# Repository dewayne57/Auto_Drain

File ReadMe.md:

# Air Compressor Automatic Drain
This project is an adaptive air compressor automatic drain system.  There are examples of products
on the market that use a timer to cycle a solenoid valve on the tank drain to release any moisture
that has condensed at the bottom of the tank.  The problem with these devices is that they cycle 
periodically (such as every 10 minutes) wether they need to or not.  For compressors that run only
sporadically, such as in a home shop, this causes aire loss and needless extra cycling of the compressor.

What this project does is sense when the compressor runs, then start a timer after it shuts off.
After some period of time (to allow condensant to accumulate), the drain valve is cycled.  The 
drain valve is then cycled again 1 hour after the last run to drain any additional accumulated 
condenstant.  After that, the drain valve is not cycled again until the compressor is run 
again.  This allows the system to efficiently drain the condensant water without needlessly 
cycling the drain valve.

## Algorithm 

### Assumptions/Conventions
- The compressor (or other sensed system) is identified as the "controlling" load. 
- The valve (or other driven system) is identified as the "controlled" load.
- The operation of the system is controlled by a state machine. 

### State Machine

| State (name)   | Stopped  | Running | Timeout |
| -------------- | -------- | ------- | ------- |
| S0 (Idle)      | S0       | S1      | S0      |
| S1 (Armed)     | S2       | S1      | S0      |
| S2 (Triggered) | S2       | S1      | S3      | 
| S3 (Drain)     | S0,S4(1) | S1      | S0      |
| S4 (Followup)  | S4       | S1      | S5      |
| S5 (Drain2)    | S0       | S1      | S0      |

- S0: Represents the idle state, where the system is waiting on the detection of the 
  controlling load to be turned on.  This is the initial state the system enters 
  after power on or a watchdog reset.
- S1: Represents the "armed" state where the controlling load has been detected to 
  be running.  As long as the controlling load is running, the system will be in this
  state. The armed state is entered from any state when the controlling load is 
  running. 
- S2: Represents the triggered state after the controlling load has stopped running
  and represents the start of the initial countdown period to operate the drain. If 
  the controlling load does not restart before the countdown timer expires, the 
  system will transition to the draining state. 
- S3: Represents the "draining" state.  This is where the drain valve is opened 
  for one second to drain the condensant water from the tank (or other operation 
  depending on application). Once the draining time has expired, the system will 
  transition to either idle or followup state (S0 or S4, see Note 1). 
- S4: This represents the followup countdown interval.  It is entered only after 
  a successfull drain cycle and  the followup  time intervals are selected by the 
  option switches.
- S5: Represents the followup drain cycle, which is initiated some time interval
  after a successful initial drain cycle if selected by the option switches. 

### Notes
1. Either S0 (Idle) or S4 (Followup) states are entered after an initial 
   drain cycle has occurred based on the setting of the option switches.  If the 
   option switches indicate no followup drain cycle, then the machine transitions
   to the idle (S0) state.  If the option switches indicate a followup drain 
   interval, the transition is to the S4 state and the followup countdown 
   interval timer is started.
2. If the controlling load is restarted at any time, any current countdown 
   interval is stopped and the state machine immediately enters the Armed 
   (s1) state.

### Option Switches: 
The option switches are a 4-position DIP switch divided into two 2-bit groups.
The first group (bits 0..1) represent the triggered countdown interval, and are
specified as: 
- 00: Cycle immediately after turn off.  There is no triggered delay, and 
  the state machine immediately cycles to the Drain (S3) state. 
- 01: The system will remain in the triggered state for 10 minutes, then 
  transition to the Drain (s3) state.
- 10: The system will remain in the triggered state for 30 minutes, then 
  transition to the Drain (S3) state. 
- 11: The system will remain in the triggered state for 1 hour (60 minutes), 
  then transition to the Drain (S3) state;

The second pair of bits (2..3) indicate the followup drain cycle, if any. 
- 00: No follow up cycle is to be used.  Transition to the Idle (S0) state
- 01: An additional followup drain cycle will occur 1 hour after the drain cycle.
- 10: An additional followup drain cycle will occur 2 hours after the drain cycle.
- 11: An additional followup drain cycle will occur 3 hours after the drain cycle.

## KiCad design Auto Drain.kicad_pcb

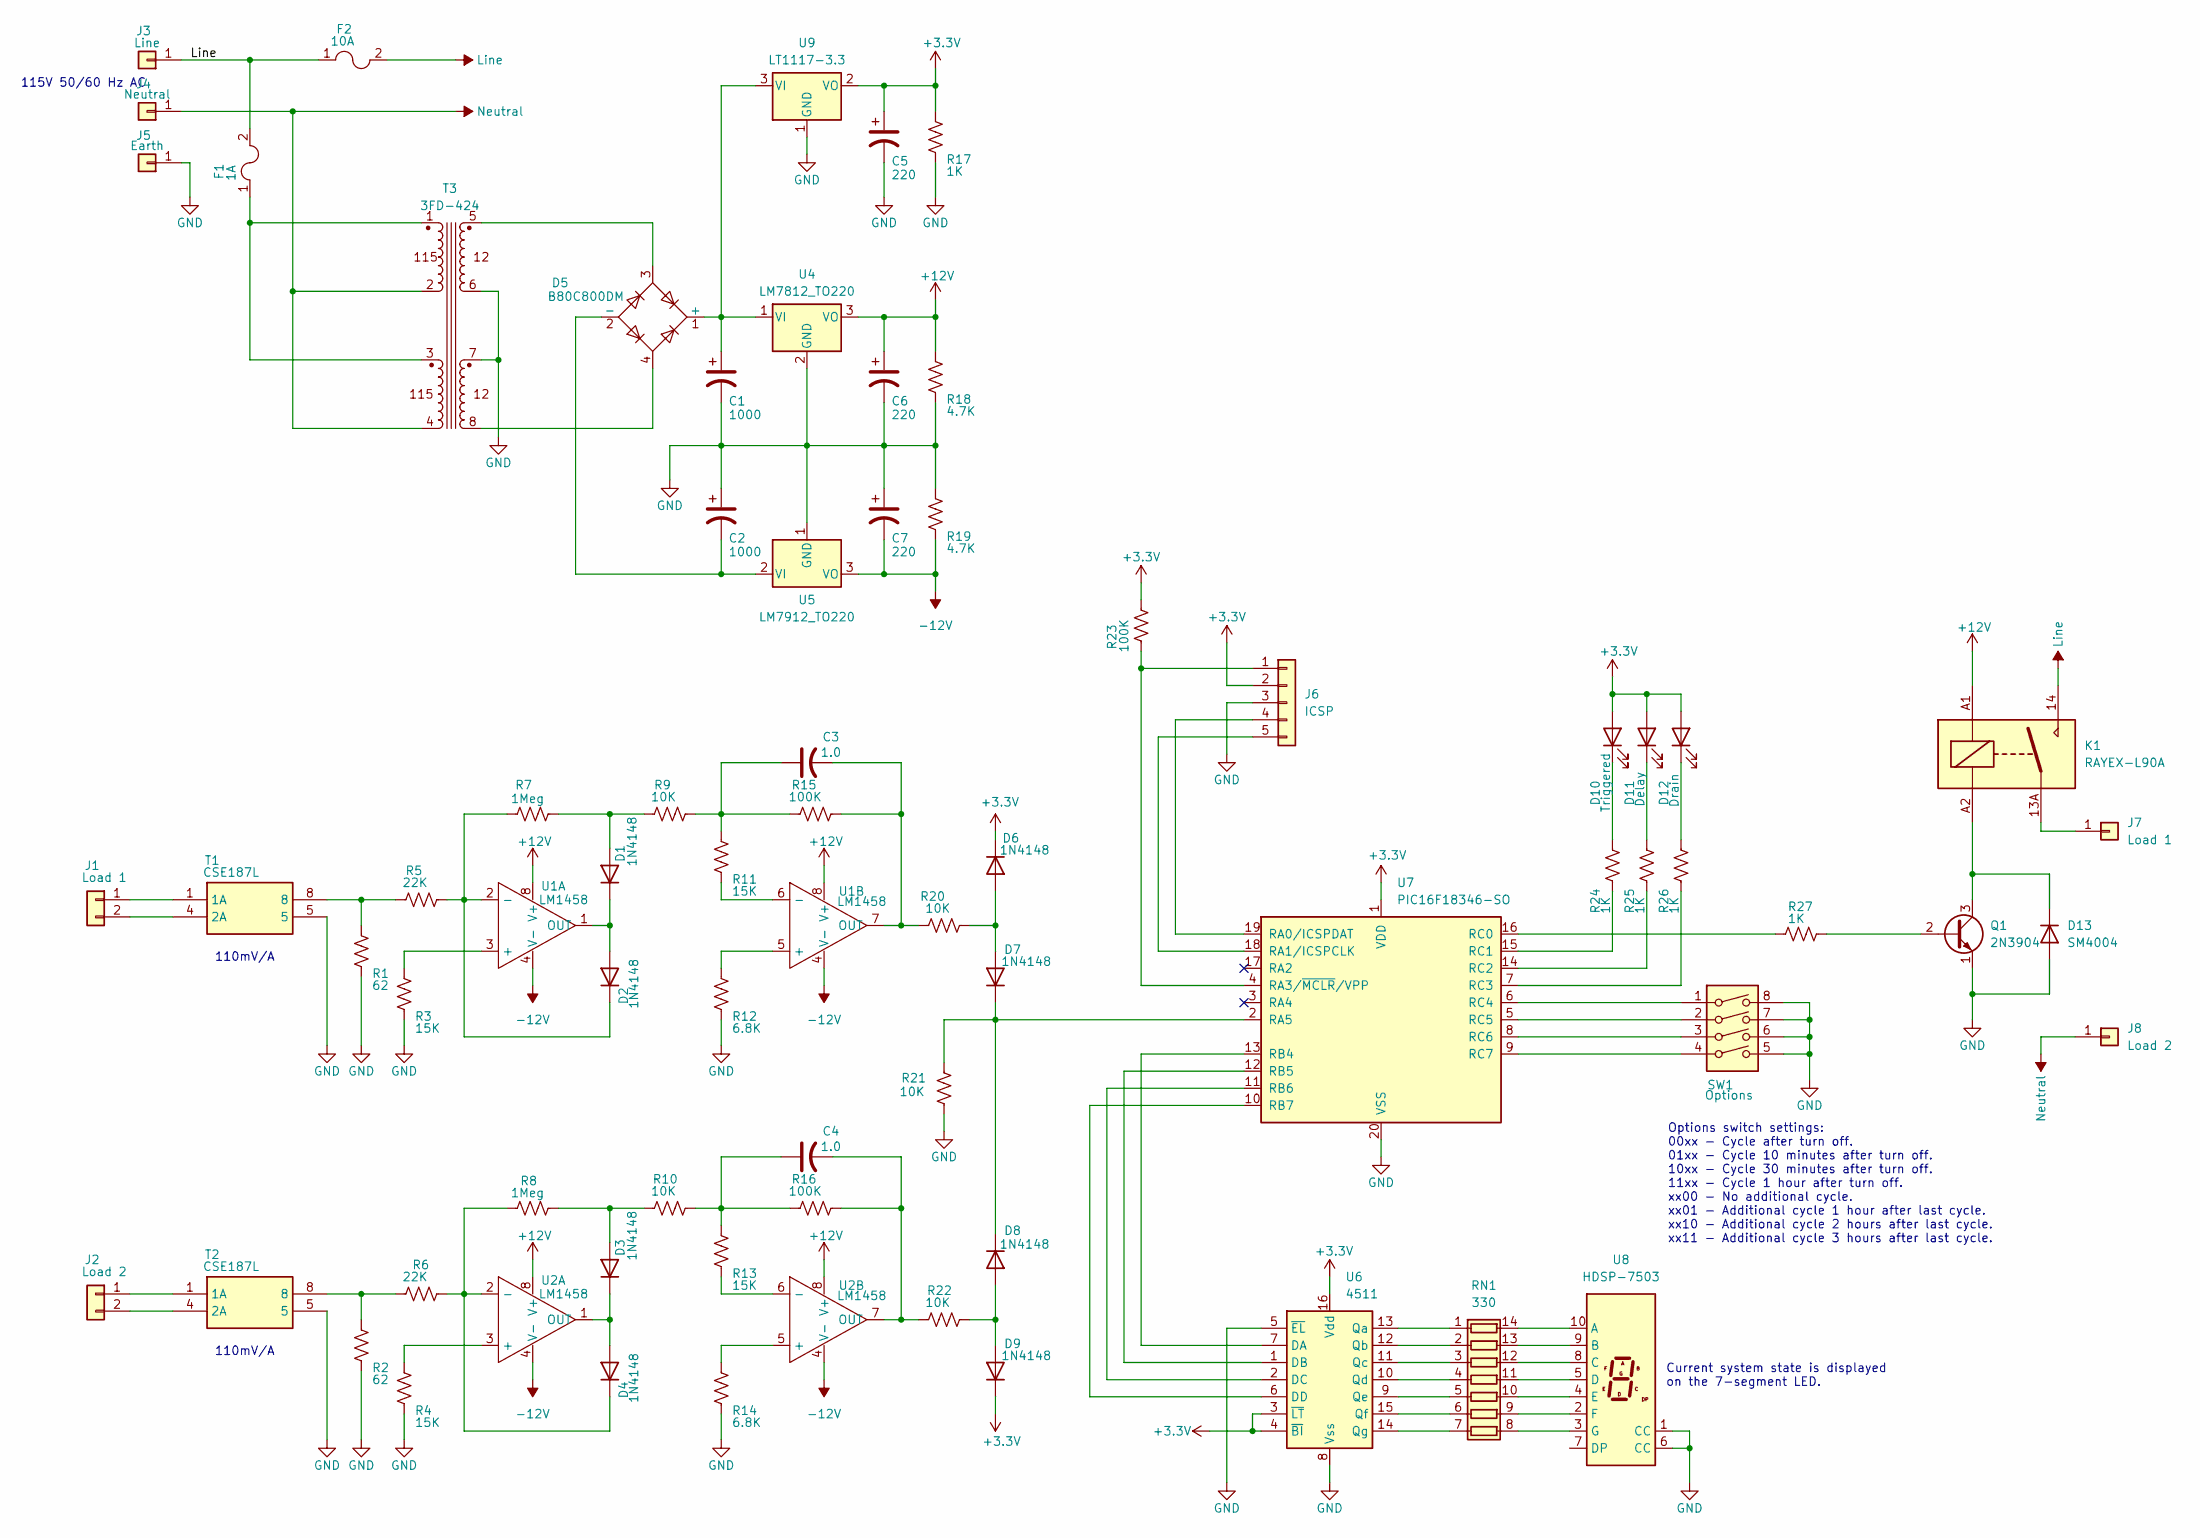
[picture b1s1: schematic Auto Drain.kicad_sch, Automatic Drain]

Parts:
C1, C2: 1000; CP_Radial_D14.0mm_P7.50mm
C3, C4: 1.0; C_Disc_D10.0mm_W2.5mm_P5.00mm
C5, C6, C7: 220; CP_Radial_D10.0mm_P3.80mm
D1, D2, D3, D4, D6, D7, D8, D9: 1N4148; D_SOD-123
D5: B80C800DM; Diode_Bridge_DIP-4_W7.62mm_P5.08mm
D10: Triggered; LED_D3.0mm
D11: Delay; LED_D3.0mm
D12: Drain; LED_D3.0mm
D13: SM4004; D_MELF
F1: 1A; Fuseholder_Clip-5x20mm_Eaton_1A5601-01_Inline_P20.80x6.76mm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
F2: 10A; Fuseholder_Clip-5x20mm_Eaton_1A5601-01_Inline_P20.80x6.76mm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
J1: Load 1; 389220002
J2: Load 2; 389220002
J3: Line; Amp Faston 250 THT
J4: Neutral; Amp Faston 250 THT
J5: Earth; Amp Faston 250 THT
J6: ICSP; PinSocket_1x05_P2.54mm_Vertical
J7: Load 1; Amp Faston 250 THT
J8: Load 2; Amp Faston 250 THT
K1: RAYEX-L90A; Relay_SPST_RAYEX-L90A
Q1: 2N3904; TO-92_Inline
R1, R2: 62; R_0805_2012Metric_Pad1.20x1.40mm_HandSolder
R3, R4, R11, R13: 15K; R_0805_2012Metric_Pad1.20x1.40mm_HandSolder
R5, R6: 22K; R_0805_2012Metric_Pad1.20x1.40mm_HandSolder
R7, R8: 1Meg; R_0805_2012Metric_Pad1.20x1.40mm_HandSolder
R9, R10, R20, R21, R22: 10K; R_0805_2012Metric_Pad1.20x1.40mm_HandSolder
R12, R14: 6.8K; R_0805_2012Metric_Pad1.20x1.40mm_HandSolder
R15, R16, R23: 100K; R_0805_2012Metric_Pad1.20x1.40mm_HandSolder
R17, R24, R25, R26, R27: 1K; R_0805_2012Metric_Pad1.20x1.40mm_HandSolder
R18, R19: 4.7K; R_0805_2012Metric_Pad1.20x1.40mm_HandSolder
RN1: 330; DIP-14_W7.62mm_LongPads
SW1: Options; DIP-8_W7.62mm_Socket_LongPads
T1, T2: CSE187L; CSE_187L; Mouser Part Number 553-CSE187L
T3: 3FD-424; 3FD-4XX
U1, U2: LM1458; DIP-8_W7.62mm_LongPads
U4: LM7812_TO220; TO-220-3_Vertical
U5: LM7912_TO220; TO-220-3_Vertical
U6: 4511; DIP-14_W7.62mm_LongPads
U7: PIC16F18346-SO; SOIC-20W_7.5x12.8mm_P1.27mm
U8: HDSP-7503; HDSP-A151
U9: LT1117-3.3; TO-92L_Inline

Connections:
+5V: C5.1, D6.1 (K), D9.1 (K), D10.2 (A), D11.2 (A), D12.2 (A), J6.2, R17.1, R23.2, U6.3 (~LT), U6.4 (~BI), U6.16 (Vdd), U7.1 (VDD), U9.2 (VO); also elsewhere on the board
+12V: C6.1, K1.A1, R18.1, U1.8 (V+), U2.8 (V+), U4.3 (VO)
-12V: C7.2, R19.2, U1.4 (V-), U2.4 (V-), U5.3 (VO)
GND: C1.2, C2.1, C5.2, C6.2, C7.1, D13.2 (A), J5.1 (Pin_1_1), J6.3, Q1.1 (E), R1.2, R2.2, R3.2, R4.2, R12.2, R14.2, R17.2, R18.2, R19.1, R21.1, SW1.5, SW1.6, SW1.7, SW1.8, T1.5, T2.5, T3.6, T3.7, U4.2 (GND), U5.1 (GND), U6.5 (~EL), U6.8 (Vss), U7.20 (VSS), U8.1 (CC), U8.6 (CC), U9.1 (GND); also elsewhere on the board
Line: F1.2, F2.1, F2.2, J3.1 (Pin_1_1), K1.14
unnamed: C3.1, R9.2, R11.1, R15.1
unnamed: C4.1, R10.2, R13.1, R16.1
unnamed: D1.2 (A), R7.2, R9.1
unnamed: D1.1 (K), D2.2 (A), U1.1 (OUT)
unnamed: D2.1 (K), R5.2, R7.1, U1.2 (-)
unnamed: D3.2 (A), R8.2, R10.1
unnamed: D3.1 (K), D4.2 (A), U2.1 (OUT)
unnamed: D4.1 (K), R6.2, R8.1, U2.2 (-)
unnamed 13: C1.1, D5.1 (+), U4.1 (VI), U9.3 (VI); also elsewhere on the board
unnamed: C2.2, D5.2 (-), U5.2 (VI)
unnamed: D5.3, T3.5
unnamed: D5.4, T3.8
unnamed: D6.2 (A), D7.2 (A), R20.2
unnamed: D7.1 (K), D8.1 (K), R21.2, U7.2 (RA5)
unnamed: D8.2 (A), D9.2 (A), R22.2
unnamed: D10.1 (K), R24.2
unnamed: D11.1 (K), R25.2
unnamed: D12.1 (K), R26.2
unnamed: D13.1 (K), K1.A2, Q1.3 (C)
unnamed: F1.1, T3.1, T3.3
unnamed: J1.1, T1.1 (1A)
unnamed: J1.2, T1.4 (2A)
unnamed: J2.1, T2.1 (1A)
unnamed: J2.2, T2.4 (2A)
unnamed: J6.1, R23.1, U7.4 (RA3/~MCLR/VPP)
unnamed: J6.4, U7.19 (RA0/ICSPDAT)
unnamed: J6.5, U7.18 (RA1/ICSPCLK)
unnamed: J7.1 (Pin_1_1), K1.13A, K1.13B
unnamed: Q1.2 (B), R27.1
unnamed: R1.1, R5.1, T1.8
unnamed: R2.1, R6.1, T2.8
unnamed: RN1.1 (R1.1), U6.13 (Qa)
unnamed: RN1.14 (R1.2), U8.10 (A)
unnamed: RN1.2 (R2.1), U6.12 (Qb)
unnamed: RN1.13 (R2.2), U8.9 (B)
unnamed: RN1.3 (R3.1), U6.11 (Qc)
unnamed: RN1.12 (R3.2), U8.8 (C)
unnamed: RN1.4 (R4.1), U6.10 (Qd)
unnamed: RN1.11 (R4.2), U8.5 (D)
unnamed: RN1.5 (R5.1), U6.9 (Qe)
unnamed: RN1.10 (R5.2), U8.4 (E)
unnamed: RN1.6 (R6.1), U6.15 (Qf)
unnamed: RN1.9 (R6.2), U8.2 (F)
unnamed: RN1.7 (R7.1), U6.14 (Qg)
unnamed: RN1.8 (R7.2), U8.3 (G)
unnamed: R3.1, U1.3 (+)
unnamed: R12.1, U1.5 (+)
unnamed: R11.2, U1.6 (-)
unnamed: C3.2, R15.2, R20.1, U1.7 (OUT)
unnamed: R4.1, U2.3 (+)
unnamed: R14.1, U2.5 (+)
unnamed: R13.2, U2.6 (-)
unnamed: C4.2, R16.2, R22.1, U2.7 (OUT)
unnamed: U6.7 (DA), U7.13 (RB4)
unnamed: U6.1 (DB), U7.12 (RB5)
unnamed: U6.2 (DC), U7.11 (RB6)
unnamed: U6.6 (DD), U7.10 (RB7)
unnamed: R27.2, U7.16 (RC0)
unnamed: R24.1, U7.15 (RC1)
unnamed: R25.1, U7.14 (RC2)
unnamed: R26.1, U7.7 (RC3)
unnamed: SW1.1, U7.6 (RC4)
unnamed: SW1.2, U7.5 (RC5)
unnamed: SW1.3, U7.8 (RC6)
unnamed: SW1.4, U7.9 (RC7)
Neutral: J4.1 (Pin_1_1), J8.1 (Pin_1_1), T3.2, T3.4

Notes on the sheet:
110mV/A
115V 50/60 Hz AC
Current system state is displayed on the 7-segment LED.
Options switch settings: 00xx - Cycle after turn off. 01xx - Cycle 10 minutes after turn off. 10xx - Cycle 30 minutes after turn off. 11xx - Cycle 1 hour after turn off. xx00 - No additional cycle. xx01 - Additional cycle 1 hour after last cycle. xx10 - Additional cycle 2 hours after last cycle. xx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

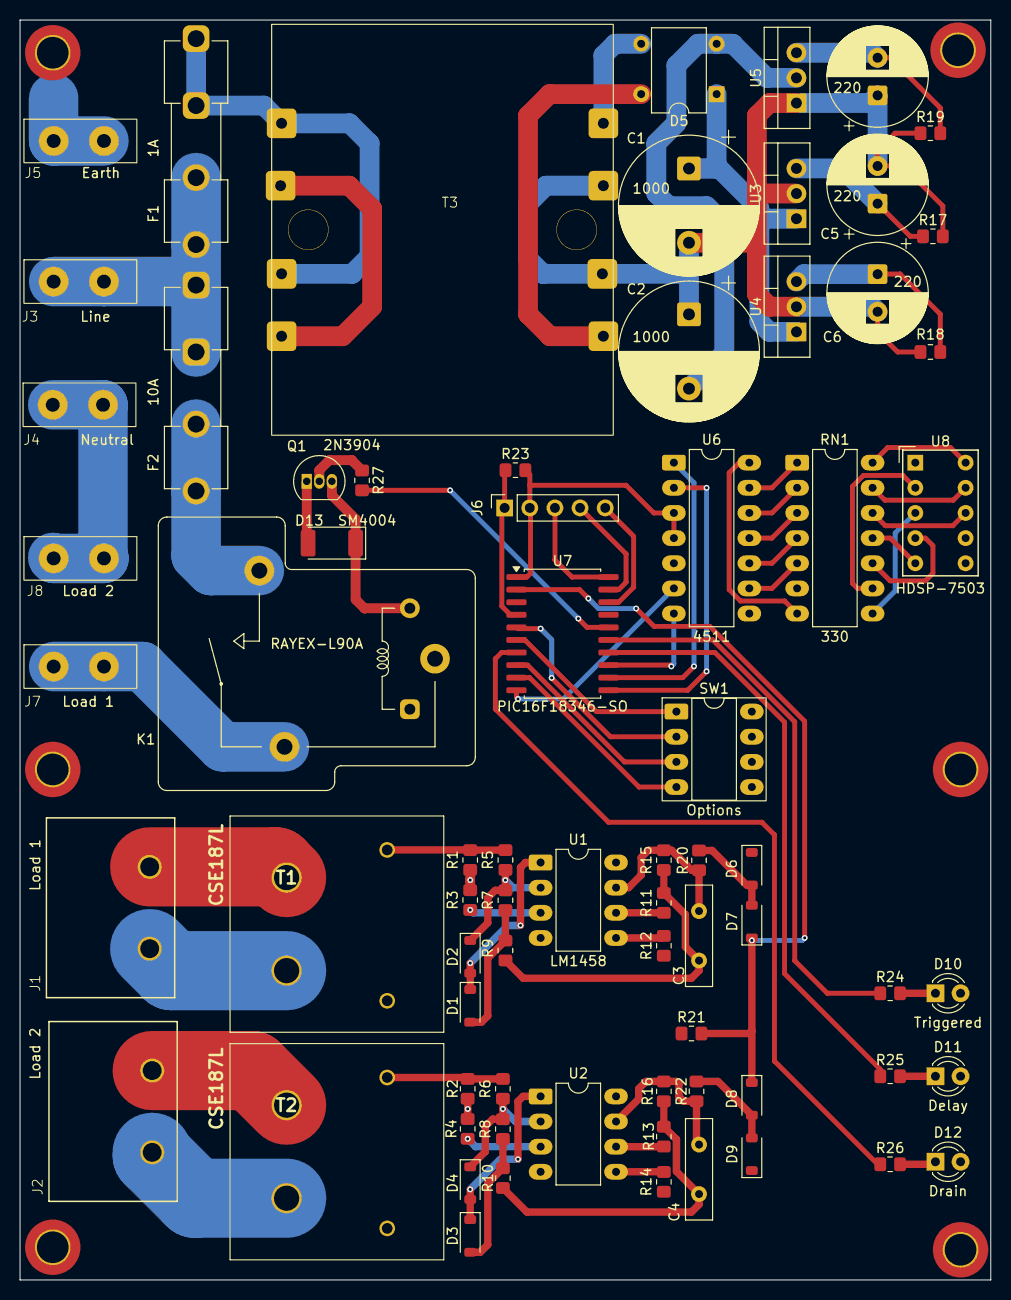
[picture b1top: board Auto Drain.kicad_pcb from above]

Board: 2 copper layers, 98.0 x 127.3 mm, 72 parts (0 on the bottom side), 70 nets.

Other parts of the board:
U3: LM7805_TO220; TO-220-3_Vertical

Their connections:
+5V: U3.3 (VO); also elsewhere on the board
GND: U3.2 (GND); also elsewhere on the board
unnamed 13: U3.1 (VI); also elsewhere on the board
